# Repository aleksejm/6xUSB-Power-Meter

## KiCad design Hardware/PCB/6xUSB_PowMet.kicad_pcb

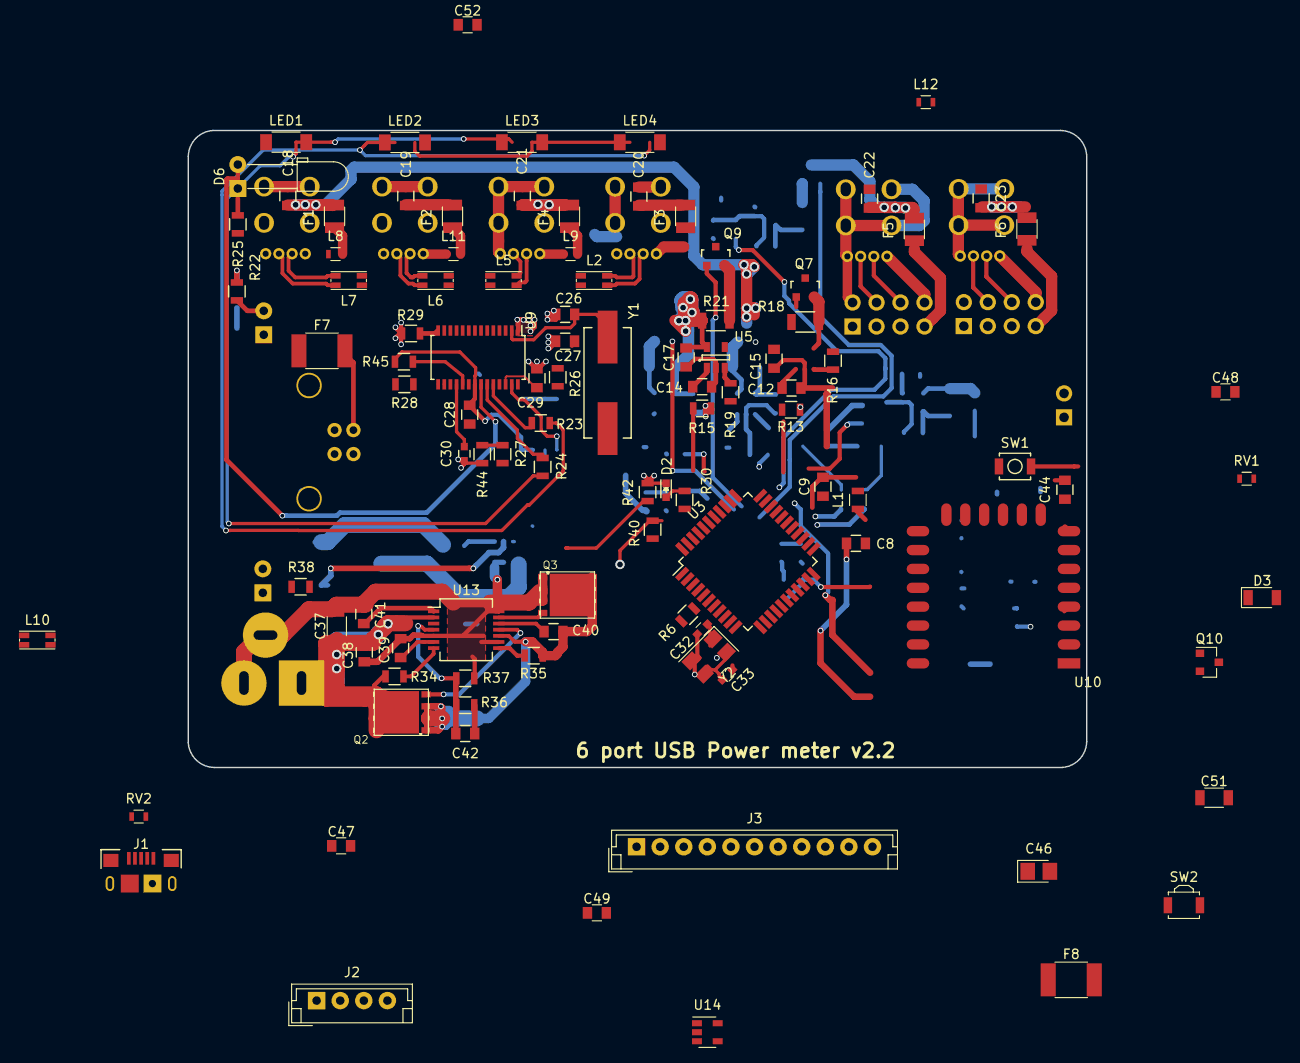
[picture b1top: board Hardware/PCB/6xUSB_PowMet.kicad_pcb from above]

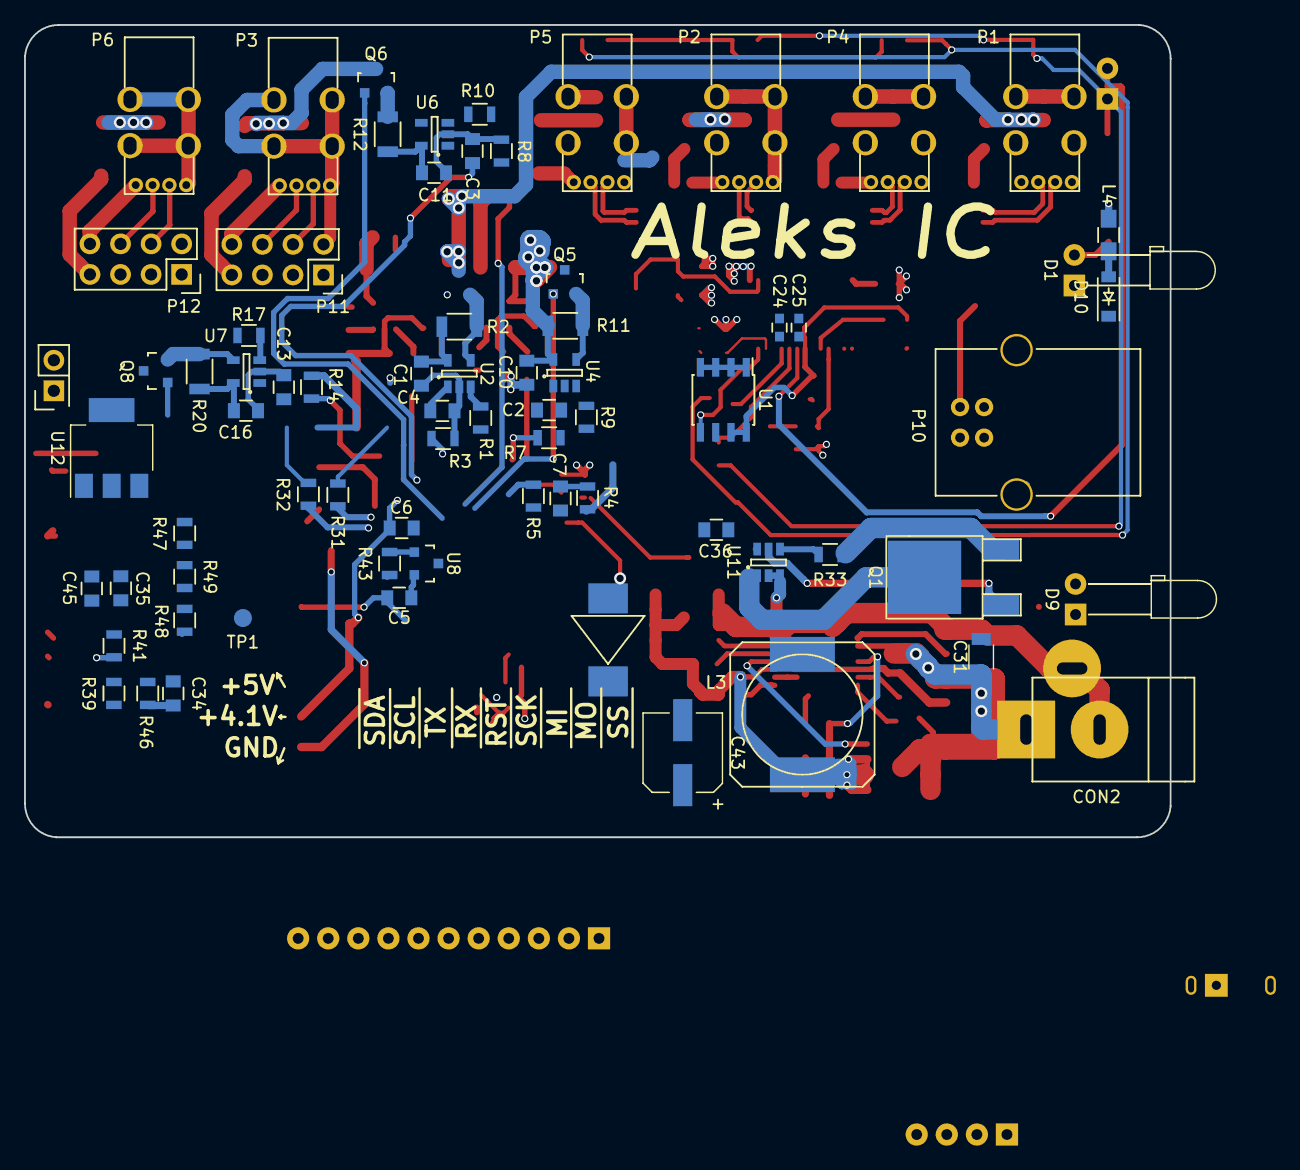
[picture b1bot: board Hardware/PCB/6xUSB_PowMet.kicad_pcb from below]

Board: 4 copper layers, 95.2 x 67.5 mm, 175 parts (73 on the bottom side), 137 nets.

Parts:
C1, C3, C4, C5, C6, C7, C8, C9, C10, C15, C16, C17, C27, C34, C35, C38, C48: 100n; C_0805
C2: 0.33uF; C_0805
C11, C12, C13, C14, C21, C22, C23, C42: 1nF; C_0805
C18, C19, C20, C28, C36, C44, C45: 10uF; C_0805
C24, C30, C33: 0.1uF; C_0603
C25, C32: 22pF; C_0603
C26, C52: 18pF; C_0805
C29: 10nF; C_0805
C31, C37, C51: 47uF; C_1206
C39: 15nF; C_0805
C40: 470nF; C_0805
C41, C47, C49: 1uF; C_0805
C43: 330uF; CP_Elec_6.3x5.8
C46: 22uF; CP_Tantalum_Case-R_EIA-2012-12_Reflow
CON2: BARREL_JACK; JACK_ALIM
D1: USB Power; LED_D3.0mm_Horizontal_O6.35mm_Z6.0mm
D2: MC Status; LED_0603
D3: CD1206-S01575; D_1206
D6: Led_Small_3mm; LED_D3.0mm_Horizontal_O6.35mm_Z6.0mm
D9: Power DC; LED_D3.0mm_Horizontal_O6.35mm_Z6.0mm
D10: SKL14; SOD-123
D11: SK152-TP; DO-214AB-SMC
F1, F2, F3, F4, F5, F6: F_Small; Fuse_SMD1206_Reflow
F7, F8: MSMF050-2; R_1812
J1: MICROUSB; USB-MICRO-B-FCI-10118193
J2: CONN_01X04; JST_EH_B04B-EH-A_04x2.50mm_Straight
J3: CONN_01X11; JST_EH_B11B-EH-A_11x2.50mm_Straight
L1: MH2029-300Y; L_0805
L2, L5, L6, L7, L10: WE-CNSW; L_CommonMode_Wuerth_WE-CNSW
L3: 4.7uH 5.2mOhm; SELF-WE-PD-XXL
L4: Bead/100MHZ/470ohm/2A; R_0805_HandSoldering
L8, L9, L11, L12: WE-CBF; L_0603
LED1, LED2, LED3, LED4: Led_Small; L_1806
P1, P2, P3, P4, P5, P6: USB_A; USB_A_Vertical
P10: USB_B
P11, P12: CONN_02X04; Socket_Strip_Straight_2x04
P13: Burn; Pin_Header_Straight_2x01
Q1: IRFR5305PBF; TO-252-2Lead
Q2: CSD16321Q5; AB2_SON5x6_FET
Q3: CSD18509Q5B; AB2_SON5x6_FET
Q5, Q6, Q7, Q8, Q9, Q10: IRLML6401; SOT-23
R1, R46: 470R; R_0805
R2, R11, R12, R18, R20, R21: 0.02R; R_1206
R3, R4, R6, R8, R9, R10, R13, R15, R16, R17, R19, R26, R27, R30, R37, R39, R40, R42: 10K; R_0805
R5: 15K; R_0805
R7, R32: 22R; R_0805
R14, R22, R23, R24, R25, R41, R43, R44, R47: 100R; R_0805
R28, R38, R45: 100K; R_0805
R29: 2.7K; R_0805
R31: 330; R_0805
R33: 470K; R_0805
R34: 237K; R_0805
R35: 1K07; R_0805
R36: 73K2; R_0805
R48, R49: 150R; R_0805
RV1, RV2: CG0603MLC-05E; L_0603
SW1: Reset; SW_SPST_B3U-1000P
SW2: Reset; SW_SPST_B3U-3000P
TP1: TEST; Measurement_Point_Round-SMD-Pad_Small
U1: 24LC02; SOIC-8_3.9x4.9mm_Pitch1.27mm
U2, U4, U5, U6, U7, U14: LT6106; SOT-23-5
U3: ATMEGA32U4-AU; LQFP-44_10x10mm_Pitch0.8mm
U8: LM4040N-4.1; SOT-23
U9: FE1.1s; TSSOP-28_4.4x9.7mm_Pitch0.65mm
U10: ESP-07v2; ESP-12E
U11: LTC4412; SOT-23-6
U12: 5v to 3.3v LDO; SOT-223-3Lead_TabPin2
U13: LM3150; SSOP-14_5.3x6.2mm_Pitch0.65mm
Y1: 12Mhz; Crystal_HC49-SD_SMD
Y2: 16.000 Mhz; Crystal_SMD_5032-4pin_5.0x3.2mm

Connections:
+3v3: C5.1, C6.1, J2.4, R3.2, R6.2, R10.2, R13.2, TP1.1, U10.8, U12.3
+4.096V: C9.1, C10.1, J2.2, R14.2, U3.42, U8.1
+5V: C2.1, C3.2, C4.2, C8.1, C15.2, C16.2, C17.2, C24.2, C27.2, C33.2, C34.2, C35.2, C48.1, D3.1, D11.2, J2.3, L1.1, Q1.3, R2.1, R4.1, R5.1, R11.1, R12.1, R14.1, R18.1, R20.1, R21.1, R22.1, R24.1, R25.1, R33.1, R41.1, R42.1, R43.1, R44.1, U2.5, U3.2, U3.14, U3.24, U3.34, U4.5, U5.5, U6.5, U7.5, U9.20, U11.6, U12.1, U14.5
/USB hub/3V3: C28.2, R38.1, R45.1, U1.7, U1.8, U9.21
/USB hub/LED1: R47.2, U1.6, U9.23
/USB hub/TESTJ: U1.5, U9.27
ADC9: J3.10, U3.26
ADC10: J3.11, U3.27
D1+: L7.2, P1.3
D1-: L7.3, P1.2
D2+: L6.2, P4.3
D2-: L6.3, P4.2
D3+: L5.2, P2.3
D3-: L5.3, P2.2
D4+: L2.2, P5.3
D4-: L2.3, P5.2
D5+: L10.1, P10.3
D5-: L10.4, P10.2
D+: R7.1, U3.4
D-: R32.1, U3.3
GND: C1.1, C2.2, C3.1, C4.1, C5.2, C6.2, C7.2, C8.2, C9.2, C10.2, C11.1, C12.1, C13.1, C14.1, C15.1, C16.1, C17.1, C18.1, C19.1, C20.1, C21.1, C22.1, C23.1, C24.1, C25.2, C26.1, C27.1, C28.1, C29.2, C31.2, C32.2, C33.1, C34.1, C35.1, C36.1, C37.2, C38.2, C39.2, C41.1, C43.2, C44.1, C45.1, C46.2, C47.1, C48.2, C49.1, C51.2, C52.1, CON2.2, CON2.3, D1.1, D2.1, D9.1, J1.5, J2.1, P1.4, P1.5, P2.4, P2.5, P4.4, P4.5, P5.4, P5.5, P10.4, P10.5, P11.1, P12.1, P13.2, Q3.1, Q3.2, Q3.3, R8.1, R9.1, R15.2, R16.2, R17.2, R19.2, R26.2, R29.2, R30.2, R37.1, R39.2, R40.2, R48.2, RV1.2, RV2.2, SW1.1, SW2.2, U1.1, U1.2, U1.3, U1.4, U2.2, U3.5, U3.15, U3.23, U3.35, U3.43, U4.2, U5.2, U6.2, U7.2, U8.2, U9.1, U10.15, U11.2, U11.3, U12.2, U13.5, U13.9, U13.14, U14.2, Y2.2, Y2.4
MC_ST: R46.1, U3.29
MISO: J3.3, U3.11
MOSI: J3.2, U3.10
unnamed: C1.2, R1.1, R6.1, SW1.2, U10.1
unnamed: C11.2, R5.2, R15.1, U3.30
unnamed: C12.2, R16.1, U2.1, U3.41
unnamed: C13.2, R17.1, U3.39, U4.1
unnamed: C14.2, R19.1, U3.37, U5.1
unnamed: C18.2, F1.2, Q10.3
unnamed: C19.2, F4.2, Q5.3
unnamed: C20.2, F3.2, Q6.3
unnamed: C21.2, R30.1, U3.40, U6.1
unnamed: C22.2, R39.1, U3.36, U7.1
unnamed: C23.2, R40.1, U3.38, U14.1
unnamed: C25.1, U3.16, Y2.3
unnamed: C26.2, U9.2, Y1.1
unnamed: C29.1, R42.2, U9.26
unnamed: C30.1, R28.1
unnamed: C30.2, R27.2, R28.2, U9.18
unnamed: C31.1, C37.1, C38.1, C51.1, CON2.1, Q2.5, Q2.6, Q2.7, Q2.8, R34.2, U13.2
unnamed: C32.1, U3.17, Y2.1
unnamed: C36.2, F2.2, Q7.3
unnamed: C39.1, U13.6
unnamed: C40.1, L3.1, Q2.1, Q2.2, Q2.3, Q3.5, Q3.6, Q3.7, Q3.8, R35.1, U13.10
unnamed: C40.2, U13.12
unnamed: C41.2, U13.1
unnamed: C42.1, C43.1, D11.1, L3.2, R31.1, R36.2
unnamed: C42.2, R36.1, R37.2, U13.4
unnamed: C44.2, F5.2, Q9.3
unnamed: C45.2, F6.2, Q8.3
unnamed: C46.1, F8.1, J1.1
unnamed: C47.2, L1.2, U3.44
unnamed: C49.2, U3.6
unnamed: C52.2, U9.3, Y1.2
unnamed: D1.2, R49.2
unnamed: D2.2, R46.2
unnamed: D6.1, R48.1
unnamed: D6.2, LED1.2, LED2.1, LED3.2, LED4.1, U9.22
unnamed: D9.2, R31.2
unnamed: D10.2, L4.1
unnamed: F1.1, L8.2
unnamed: F2.1, L11.2
unnamed: F3.1, P11.7
unnamed: F4.1, L9.2
unnamed: F5.1, L12.2
unnamed: F6.1, P12.7
unnamed: F7.2, P10.1
unnamed: J1.2, R32.2, RV2.1
unnamed: J1.3, R7.2, RV1.1
unnamed: L2.1, U9.5
unnamed: L2.4, U9.4
unnamed: L5.1, U9.7
unnamed: L5.4, U9.6
unnamed: L6.1, U9.9
unnamed: L6.4, U9.8
unnamed: L7.1, U9.11
unnamed: L7.4, U9.10
unnamed: L8.1, P1.1
unnamed: L9.1, P2.1
unnamed: L10.2, U9.16
unnamed: L10.3, U9.15
unnamed: L11.1, P4.1
unnamed: L12.1, P5.1
unnamed: LED1.1, LED4.2, R23.1
unnamed: LED2.2, LED3.1, R47.1
unnamed: P3.4, P3.5, P11.2
unnamed: P3.3, P11.4
unnamed: P3.2, P11.6
unnamed: P3.1, P11.8
unnamed: P6.4, P6.5, P12.2
unnamed: P6.3, P12.4
unnamed: P6.2, P12.6
unnamed: P6.1, P12.8
unnamed: P13.1, R10.1, U10.18
unnamed: Q1.1, U11.5
unnamed: Q2.4, U13.11
unnamed: Q3.4, U13.13
unnamed: Q5.2, R11.2, U4.4
unnamed: Q6.2, R12.2, U5.4
unnamed: Q7.2, R18.2, U6.4
unnamed: Q8.2, R20.2, U7.4
unnamed: Q9.2, R21.2, U14.4
unnamed: Q10.2, R2.2, U2.4
unnamed: R1.2, U10.4
unnamed: R3.1, U10.3
unnamed: R9.2, U10.16
unnamed: R13.1, U10.17
unnamed: R22.2, U2.3
unnamed: R23.2, U9.24
unnamed: R24.2, U4.3
unnamed: R25.2, U5.3
unnamed: R29.1, U9.14
unnamed: R34.1, U13.7
unnamed: R35.2, U13.8
unnamed: R38.2, U9.17
unnamed: R41.2, U6.3
unnamed: R43.2, U7.3
unnamed: R44.2, U14.3
unnamed: R45.2, U9.19
PB0_40: R26.1, R33.2, U3.28, U11.4
RST: D3.2, J3.5, R4.2, SW2.1, U3.13
RXD: J3.6, U3.20, U10.22
SCK: J3.4, U3.9
SCL: J3.8, U3.18
SDA: J3.9, U3.19
SS: J3.1, U3.8
TXD: J3.7, U3.21, U10.21
USB_1: Q10.1, U3.1
USB_2: Q7.1, U3.12
USB_3: Q5.1, U3.32
USB_4: Q9.1, U3.33
USB_5: Q6.1, U3.31
USB_6: Q8.1, U3.22
USB_P: F7.1, L4.2, R49.1, U3.25
VBUS: C7.1, F8.2, R8.2, U3.7
VREG: D10.1, Q1.2, R27.1, U11.1

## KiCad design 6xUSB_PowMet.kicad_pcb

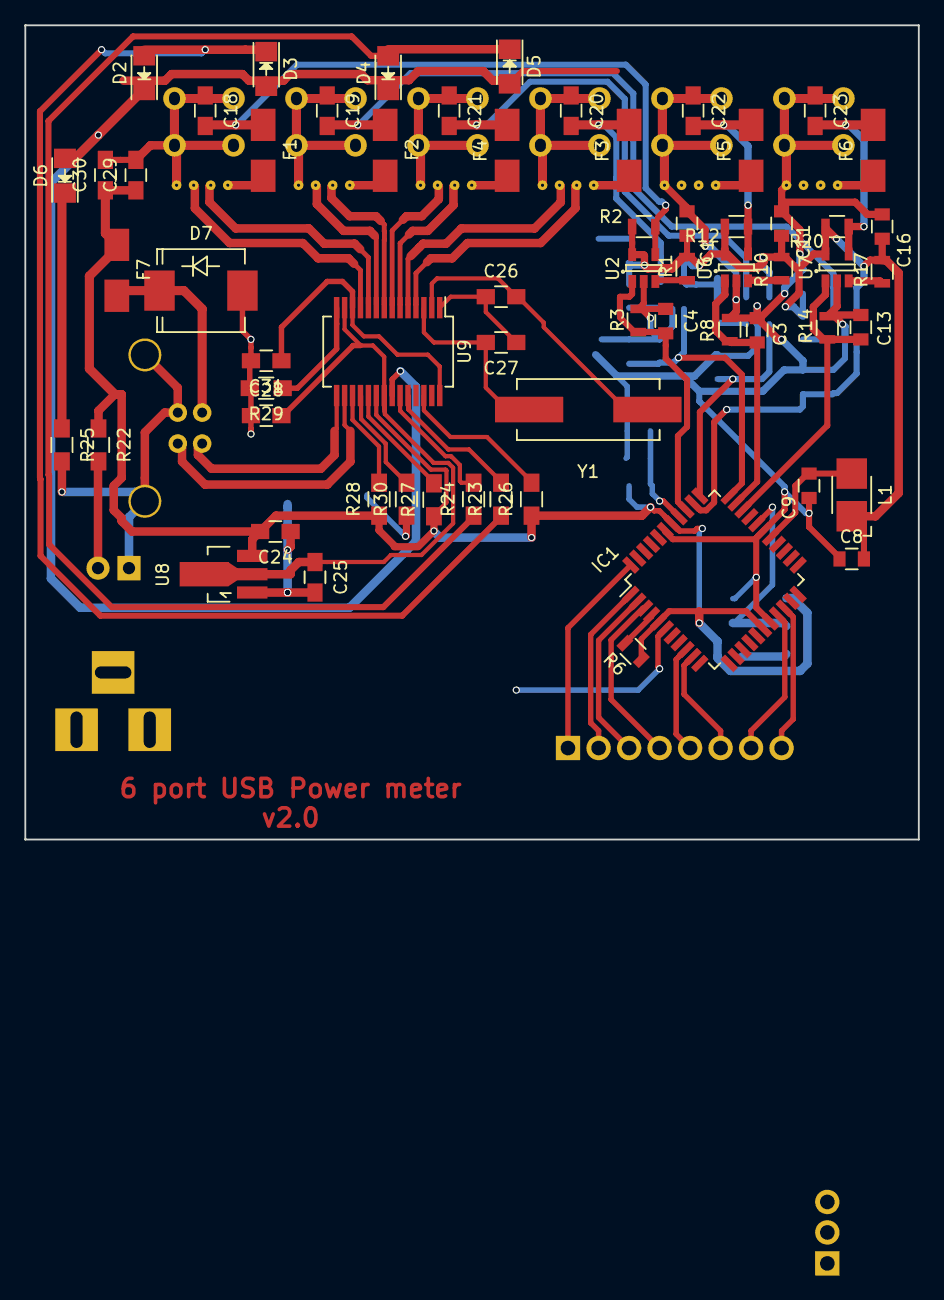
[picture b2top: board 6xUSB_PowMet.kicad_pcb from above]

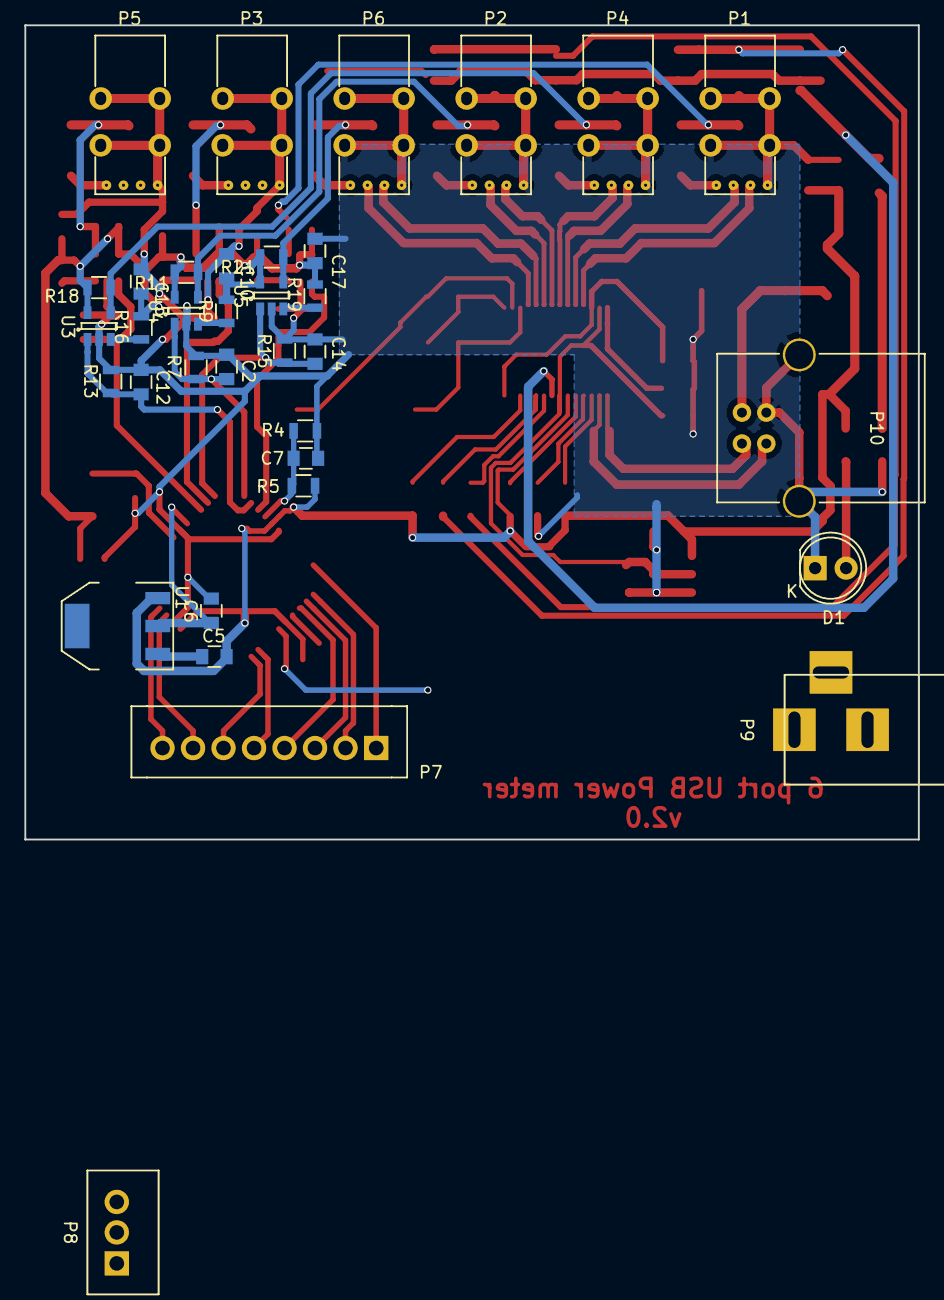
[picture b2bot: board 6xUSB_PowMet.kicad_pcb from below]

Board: 2 copper layers, 73.2 x 66.8 mm, 97 parts (35 on the bottom side), 65 nets.

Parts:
C1, C5, C8, C9, C10, C11, C15, C16, C17: 100n; C_0805
C2, C3, C4, C7, C12, C13, C14: 1n; C_0805
C6: 10uF; C_0805
C18, C19, C20, C21, C22, C23, C28, C30, C31: 10uF; C_0805_HandSoldering
C24, C25: 4.7uF; C_0805_HandSoldering
C26, C27: 10pF; C_0805_HandSoldering
C29: 10nF; C_0805_HandSoldering
D1: Power; LED-5MM
D2, D3, D4, D5, D6: Led_Small; LED_1206
D7: 5.1V; SMC_Standard
F1, F2, F3, F4, F5, F6, F7: F_Small; Fuse_SMD1206_HandSoldering
IC1: ATMEGA32-M; TQFP-44_10x10mm_Pitch0.8mm
L1: 10uH; Inductor_1212
P1, P2, P3, P4, P5, P6: USB_A; USB_A_Vertical
P7: CONN_01X08; Wafer_Vertical22.5x5.8x7RM2.5-8
P8: CONN_01X03; Wafer_Vertical10x5.8x7RM2.5-3
P9: CONN_01X02; BARREL_JACK
P10: USB_B
R1, R9, R10, R16, R17, R19: 100R; R_0805
R2, R11, R12, R18, R20, R21: 0.01R; R_0805
R3, R4, R7, R8, R13, R14, R15: 10K; R_0805
R5: 14K; R_0805
R6: 10k; R_0805
R22, R23, R24, R25: 330; R_0805_HandSoldering
R26, R27, R28, R30: 10K; R_0805_HandSoldering
R29: 2.7K; R_0805_HandSoldering
U1: LM1117MP-2.5; SOT-223
U2, U3, U4, U5, U6, U7: LT6106; SOT-23-5
U8: AP1117E33; SOT89-3_Housing_Handsoldering
U9: FE1.1s; SSOP-28_5.3x10.2mm_Pitch0.65mm
Y1: 12Mhz; Crystal_HC49-SD_SMD

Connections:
+2.5V: C6.1, IC1.29, P8.2, U1.2
+5V: C1.2, C5.1, C8.2, C10.2, C11.2, C15.2, C16.2, C17.2, C24.2, C29.1, C30.1, D7.1, F7.1, F7.2, IC1.5, IC1.17, IC1.38, L1.1, P8.3, P9.1, P10.1, R1.1, R2.1, R5.1, R6.1, R9.1, R10.1, R11.1, R12.1, R16.1, R17.1, R18.1, R19.1, R20.1, R21.1, R22.1, R26.1, R27.1, R28.1, U1.3, U2.5, U3.5, U4.5, U5.5, U6.5, U7.5, U8.3, U9.20
/USB hub/1V8: C31.1, U9.12, U9.28
/USB hub/3V3: C25.1, C28.2, U8.2, U9.13, U9.21
D1+: P1.3, U9.11
D1-: P1.2, U9.10
D2+: P4.3, U9.9
D2-: P4.2, U9.8
D3+: P2.3, U9.7
D3-: P2.2, U9.6
D4+: P6.3, U9.5
D4-: P6.2, U9.4
D5+: P10.3, U9.16
D5-: P10.2, U9.15
GND: C1.1, C2.1, C3.1, C4.1, C5.2, C6.2, C7.1, C8.1, C9.1, C10.1, C11.1, C12.1, C13.1, C14.1, C15.1, C16.1, C17.1, C18.1, C19.1, C20.1, C21.1, C22.1, C23.1, C24.1, C25.2, C28.1, C29.2, C30.2, C31.2, D1.1, D7.2, IC1.6, IC1.18, IC1.28, IC1.39, P1.4, P1.5, P2.4, P2.5, P3.4, P3.5, P4.4, P4.5, P5.4, P5.5, P6.4, P6.5, P8.1, P9.2, P10.4, P10.5, R3.1, R4.1, R7.1, R8.1, R13.1, R14.1, R15.1, R25.2, R29.2, R30.1, U1.1, U2.2, U3.2, U4.2, U5.2, U6.2, U7.2, U8.1
MISO: IC1.2, P7.3
MOSI: IC1.1, P7.2
unnamed: C2.2, IC1.34, R7.2, U4.1
unnamed: C3.2, IC1.32, R8.2, U6.1
unnamed: C4.2, IC1.36, R3.2, U2.1
unnamed: C7.2, IC1.37, R4.2, R5.2
unnamed: C9.2, IC1.27, L1.2
unnamed: C12.2, IC1.35, R13.2, U3.1
unnamed: C13.2, IC1.31, R14.2, U7.1
unnamed: C14.2, IC1.33, R15.2, U5.1
unnamed: C18.2, F1.1, R2.2, U2.4
unnamed: C19.2, F2.1, R18.2, U3.4
unnamed: C20.2, F3.2, R21.2, U5.4
unnamed: C21.2, F4.2, R11.2, U4.4
unnamed: C22.2, F5.2, R12.2, U6.4
unnamed: C23.2, F6.2, R20.2, U7.4
unnamed: C26.1, C27.1, U9.1
unnamed: C26.2, U9.2, Y1.1
unnamed: C27.2, U9.3, Y1.2
unnamed: D1.2, R22.2
unnamed: D2.1, D3.2, D4.1, D5.2, D6.2, U9.22
unnamed: D2.2, D3.1, R23.1
unnamed: D4.2, D5.1, R24.1
unnamed: D6.1, R25.1
unnamed: F1.2, P1.1
unnamed: F2.2, P4.1
unnamed: F3.1, P6.1
unnamed: F4.1, P2.1
unnamed: F5.1, P3.1
unnamed: F6.1, P5.1
unnamed: IC1.4, R6.2
unnamed: R1.2, U2.3
unnamed: R9.2, U4.3
unnamed: R10.2, U6.3
unnamed: R16.2, U3.3
unnamed: R17.2, U7.3
unnamed: R19.2, U5.3
unnamed: R23.2, U9.24
unnamed: R24.2, U9.23
unnamed: R26.2, U9.26
unnamed: R27.2, U9.19
unnamed: R28.2, U9.17
unnamed: R29.1, U9.14
unnamed: R30.2, U9.18
RXD: IC1.9, P7.5
SCK: IC1.3, P7.4
SCL: IC1.19, P7.7
SDA: IC1.20, P7.8
SS: IC1.44, P7.1
TXD: IC1.10, P7.6

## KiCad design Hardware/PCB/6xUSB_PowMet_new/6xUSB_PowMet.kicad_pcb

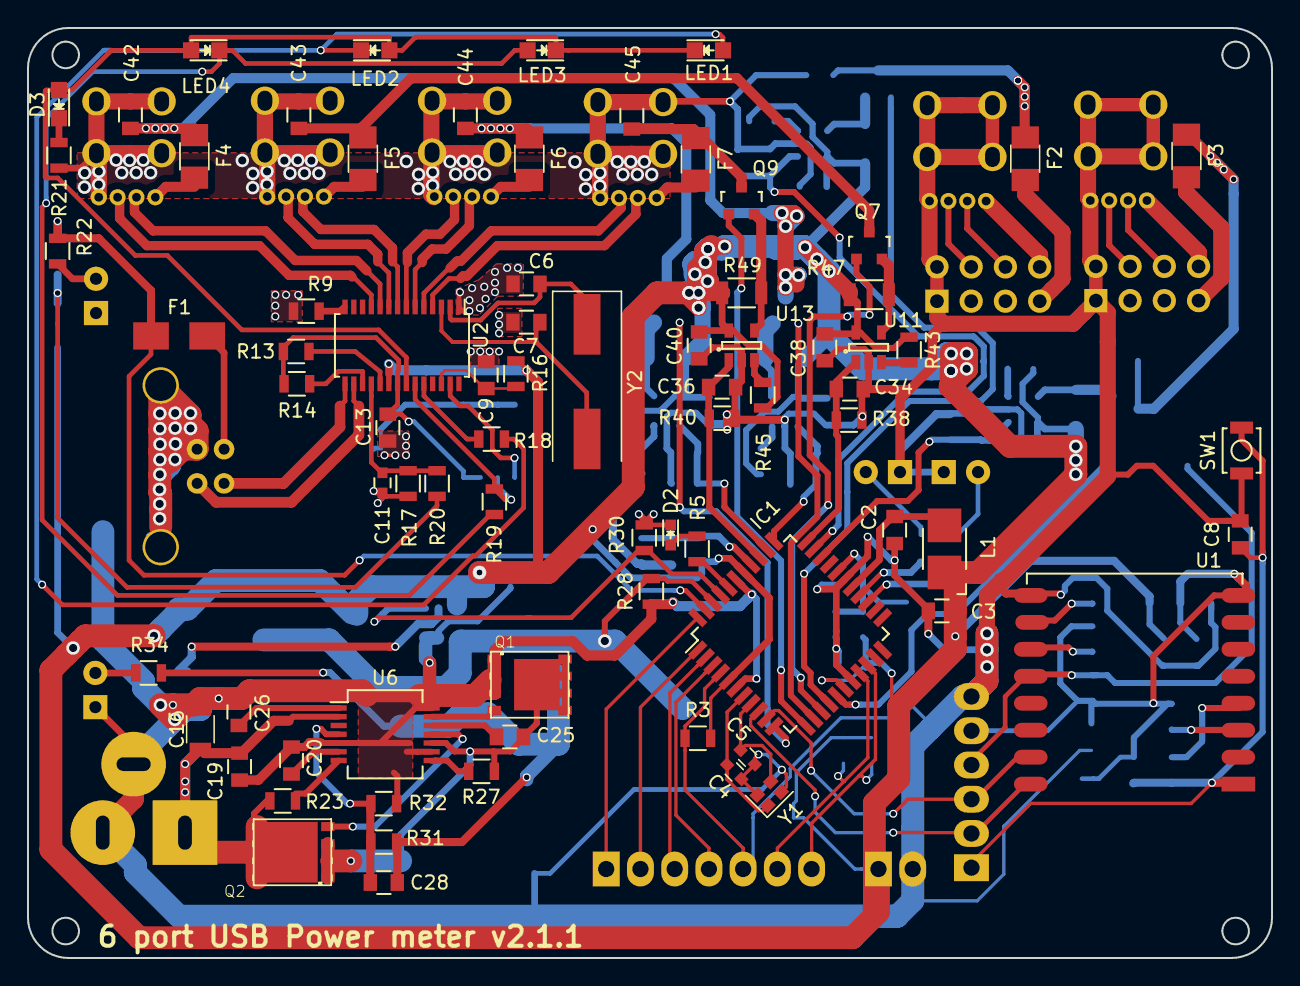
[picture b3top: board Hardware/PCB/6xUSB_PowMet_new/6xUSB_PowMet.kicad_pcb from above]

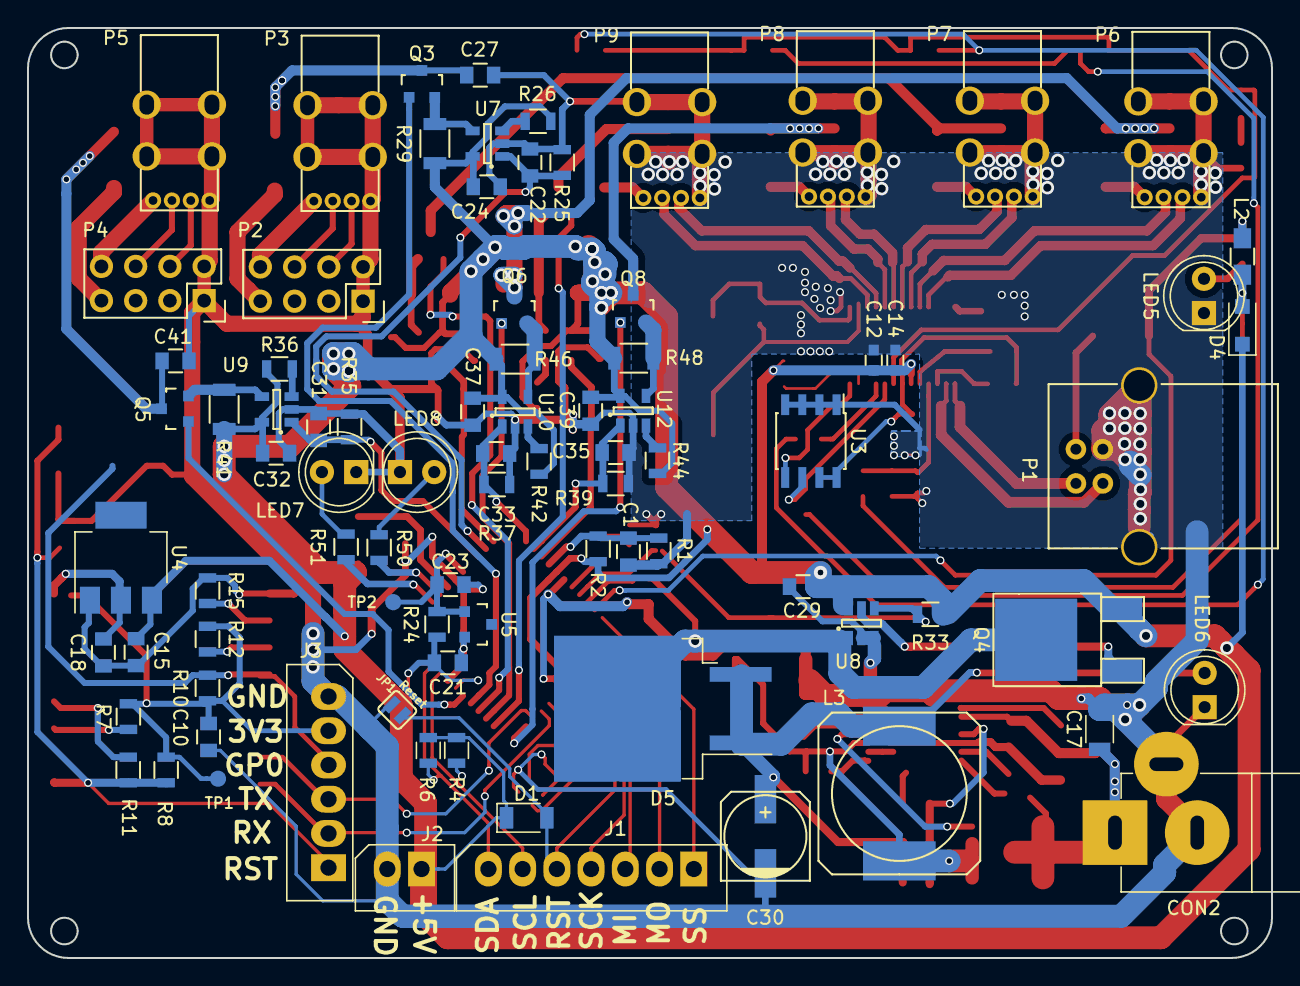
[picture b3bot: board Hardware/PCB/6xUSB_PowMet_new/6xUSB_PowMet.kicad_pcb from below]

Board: 2 copper layers, 92.3 x 69.0 mm, 161 parts (85 on the bottom side), 115 nets.

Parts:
C1: 1n; C_0805
C2, C3, C8, C21, C23: 100n; C_0805
C4, C5: 22pF; C_0603
C6, C7: 18pF; C_0805
C9: 10nF; C_0805
C10: 100uF; C_0805
C11, C12, C14: 0.1uF; C_0603
C13, C15, C27, C41, C42, C43, C44, C45: 10uF; C_0805
C16, C17: 22uF; C_1206
C18, C19, C24, C29, C32, C37, C38, C39, C40: 100nF; C_0805
C20: 15nF; C_0805
C22, C31, C33, C34, C35, C36: 1nF; C_0805
C25: 470nF; C_0805
C26: 1uF; C_0805
C28: 470pF; C_0805
C30: 220uF; c_elec_6.3x7.7
CON2: JACK; JACK_ALIM
D1: CD1206-S01575; D_1206
D2: MC Stat; LED_0603
D3: Act; LED_0805
D4: SKL14; D_SOD-123F
D5: SK2030YD2; TO-263-2
F1: 500mA; Fuse_SMD1206_HandSoldering
F2, F3, F4, F5, F6, F7: F_Small; Fuse_SMD1206_Wave
IC1: ATMEGA32-M; TQFP-44_10x10mm_Pitch0.8mm
J1: Conn_01x07; Molex_SPOX-5267_22-03-5075_07x2.54mm_Straight
J2: Conn_01x02; Molex_SPOX-5267_22-03-5025_02x2.54mm_Straight
J3: Conn_01x06; Molex_SPOX-5267_22-03-5065_06x2.54mm_Straight
JP1: Reset; SMT-JUMPER_2_NO_SILK
L1: 10uH; Inductor_1212
L2: 100Mhz 470ohm; R_0805_HandSoldering
L3: 2.2uH; SELF-WE-PD-XXL
LED1: P4; LED_0805
LED2: P2; LED_0805
LED3: P3; LED_0805
LED4: P1; LED_0805
LED5: U_PW; LED_D5.0mm
LED6: DC_PW; LED_D5.0mm
LED7: ST_USB; LED_D5.0mm
LED8: ST_DC; LED_D5.0mm
P1: USB_B
P2, P4: CONN_02X04; Socket_Strip_Straight_2x04
P3, P5, P6, P7, P8, P9: USB_A; USB_A_Vertical
Q1: CSD17577Q5A; AB2_SON5x6_FET
Q2: CSD16342Q5A; AB2_SON5x6_FET
Q3, Q5, Q6, Q7, Q8, Q9: IRLML6401; SOT-23
Q4: IRFR5305PBF; TO-252-2Lead
R1, R3, R4, R6, R7, R8, R10, R12, R15, R16, R20, R28, R30, R32: 10K; R_0805
R2: 15K; R_0805
R5, R11, R18, R19, R21, R22, R34, R50, R51: 470; R_0805
R9: 2.7K; R_0805
R13, R14, R17, R23: 100K; R_0805
R24: 100; R_0805
R25, R35, R37, R38, R39, R40: 1K; R_0805
R26, R36, R42, R43, R44, R45: 100R; R_0805
R27: 1K07; R_0805
R29, R41, R46, R47, R48, R49: 0.02R; R_1206
R31: 73K2; R_0805
R33: 470K; R_0805
SW1: Reset; SW_SPST_B3U-1000P
TP1: 3.3V; TEST-SMD-SMALL
TP2: 4.096V; TEST-SMD-SMALL
U1: ESP-12; ESP-12_mod
U2: FE1.1s; TSSOP-28_4.4x9.7mm_Pitch0.65mm
U3: 24LC02; SOIC-8_3.9x4.9mm_Pitch1.27mm
U4: AP1117E33; SOT-223
U5: LM4040; SOT-23
U6: LM3150; SSOP-14_5.3x6.2mm_Pitch0.65mm
U7, U9, U10, U11, U12, U13: LT6106; SOT-23-5
U8: LTC4412; SOT-23-6
Y1: 16MHz; Crystal_SMD_2016-4pin_2.0x1.6mm
Y2: 12Mhz; Crystal_SMD_HC49-SD

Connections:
+3V3: C10.1, C18.1, J3.5, R7.1, R8.1, R10.1, R12.1, TP1.1, U1.8, U4.2
+5V: C3.2, C12.2, C14.2, C15.1, C21.1, C24.2, C29.1, C32.2, C37.2, C38.2, C39.2, C40.2, D1.1, D4.1, IC1.5, IC1.17, IC1.38, J2.1, L1.1, Q4.3, R2.1, R3.2, R4.1, R6.1, R16.2, R24.2, R26.2, R29.1, R33.1, R36.2, R41.1, R42.2, R43.2, R44.2, R45.2, R46.1, R47.1, R48.1, R49.1, U2.20, U4.3, U7.5, U8.6, U9.5, U10.5, U11.5, U12.5, U13.5
/3V3: C13.1, R13.1, R14.1, U2.21, U3.7, U3.8
/+4.096V: C23.1, IC1.29, R24.1, TP2.1, U5.1
/D+1: P6.3, U2.11
/D+2: P7.3, U2.9
/D+3: P8.3, U2.7
/D+4: P9.3, U2.5
/D+5: P1.3, U2.16
/D-1: P6.2, U2.10
/D-2: P7.2, U2.8
/D-3: P8.2, U2.6
/D-4: P9.2, U2.4
/D-5: P1.2, U2.15
/GPIO0: J3.4, R10.2, U1.12
/LED1: R19.2, U2.23, U3.6
/MC_ST: IC1.40, R5.1
/MISO: IC1.2, J1.3
/MOSI: IC1.1, J1.2
/PB0_40: IC1.41, R30.1, R33.2, U8.4
/PB1_41: D5.2, IC1.42, Q4.2, R28.2, U8.1
/RST-ESP: C8.1, J3.1, R8.2, R11.2, SW1.2, U1.1
/RXD: IC1.9, J3.2, U1.16
/Reset: D1.2, IC1.4, J1.5, JP1.1, R3.1
/SCK: IC1.3, J1.4
/SCL: IC1.19, J1.6, R4.2
/SDA: IC1.20, J1.7, R6.2
/SS: IC1.44, J1.1
/ST_DC: IC1.26, R50.1
/ST_USB: IC1.25, R51.1
/TESTJ: U2.27, U3.5
/TXD: IC1.10, J3.3, U1.15
/USB1: IC1.13, Q6.1
/USB2: IC1.14, Q7.1
/USB3: IC1.11, Q8.1
/USB4: IC1.12, Q9.1
/USB5: IC1.16, Q5.1
/USB6: IC1.15, Q3.1
/USB_P: F1.1, IC1.43, L2.1, R22.1
/U_Sens1: C33.1, IC1.34, R37.1, U10.1
/U_Sens2: C34.1, IC1.33, R38.1, U11.1
/U_Sens3: C35.1, IC1.35, R39.1, U12.1
/U_Sens4: C36.1, IC1.36, R40.1, U13.1
/U_Sens5: C31.1, IC1.31, R35.1, U9.1
/U_Sens6: C22.1, IC1.32, R25.1, U7.1
/VBUSM: D4.2, L2.2, R20.1
GND: C1.1, C2.1, C3.1, C4.1, C5.1, C6.2, C7.2, C8.2, C9.1, C10.2, C11.2, C12.1, C13.2, C14.1, C15.2, C16.2, C17.2, C18.2, C19.2, C20.1, C21.2, C22.2, C23.2, C24.1, C26.1, C27.2, C29.2, C30.2, C31.2, C32.1, C33.2, C34.2, C35.2, C36.2, C37.1, C38.1, C39.1, C40.1, C41.2, C42.2, C43.2, C44.2, C45.2, CON2.2, CON2.3, D2.1, IC1.6, IC1.18, IC1.28, IC1.39, J2.2, J3.6, JP1.2, LED5.1, LED6.1, LED7.1, LED8.1, P1.4, P1.5, P2.1, P2.2, P3.4, P3.5, P4.1, P4.2, P5.4, P5.5, P6.4, P6.5, P7.4, P7.5, P8.4, P8.5, P9.4, P9.5, Q1.1, Q1.2, Q1.3, R1.1, R9.1, R15.1, R17.1, R21.2, R25.2, R28.1, R30.2, R32.1, R35.2, R37.2, R38.2, R39.2, R40.2, SW1.1, U1.9, U2.1, U3.1, U3.2, U3.3, U3.4, U4.1, U5.2, U6.5, U6.9, U6.14, U7.2, U8.2, U8.3, U9.2, U10.2, U11.2, U12.2, U13.2, Y1.2, Y1.4
unnamed: C1.2, IC1.37, R1.2, R2.2
unnamed: C2.2, IC1.27, L1.2
unnamed: C4.2, IC1.7, Y1.1
unnamed: C5.2, IC1.8, Y1.3
unnamed: C6.1, U2.2, Y2.1
unnamed: C7.1, U2.3, Y2.2
unnamed: C9.2, R16.1, U2.26
unnamed: C11.1, R17.2, R20.2, U2.18
unnamed: C16.1, C17.1, C19.1, CON2.1, Q2.5, Q2.6, Q2.7, Q2.8, R23.2, U6.2
unnamed: C20.2, U6.6
unnamed: C25.1, L3.1, Q1.5, Q1.6, Q1.7, Q1.8, Q2.1, Q2.2, Q2.3, R27.1, U6.10
unnamed: C25.2, U6.12
unnamed: C26.2, U6.1
unnamed: C27.1, F2.1, Q3.3
unnamed: C28.1, C30.1, D5.1, D5.3, L3.2, R31.2, R34.1
unnamed: C28.2, R31.1, R32.2, U6.4
unnamed: C41.1, F3.1, Q5.3
unnamed: C42.1, F4.1, Q6.3
unnamed: C43.1, F5.1, Q7.3
unnamed: C44.1, F6.1, Q8.3
unnamed: C45.1, F7.1, Q9.3
unnamed: D2.2, R5.2
unnamed: D3.1, R21.1
unnamed: D3.2, LED1.1, LED2.2, LED3.1, LED4.2, U2.22
unnamed: F1.2, P1.1
unnamed: F2.2, P2.7
unnamed: F3.2, P4.7
unnamed: F4.2, P6.1
unnamed: F5.2, P7.1
unnamed: F6.2, P8.1
unnamed: F7.2, P9.1
unnamed: LED1.2, LED2.1, R18.1
unnamed: LED3.2, LED4.1, R19.1
unnamed: LED5.2, R22.2
unnamed: LED6.2, R34.2
unnamed: LED7.2, R51.2
unnamed: LED8.2, R50.2
unnamed: P2.4, P3.3
unnamed: P2.6, P3.2
unnamed: P2.8, P3.1
unnamed: P4.4, P5.3
unnamed: P4.6, P5.2
unnamed: P4.8, P5.1
unnamed: Q1.4, U6.13
unnamed: Q2.4, U6.11
unnamed: Q3.2, R29.2, U7.4
unnamed: Q4.1, U8.5
unnamed: Q5.2, R41.2, U9.4
unnamed: Q6.2, R46.2, U10.4
unnamed: Q7.2, R47.2, U11.4
unnamed: Q8.2, R48.2, U12.4
unnamed: Q9.2, R49.2, U13.4
unnamed: R7.2, U1.3
unnamed: R9.2, U2.14
unnamed: R11.1, U1.4
unnamed: R12.2, U1.11
unnamed: R13.2, U2.19
unnamed: R14.2, U2.17
unnamed: R15.2, U1.10
unnamed: R18.2, U2.24
unnamed: R23.1, U6.7
unnamed: R26.1, U7.3
unnamed: R27.2, U6.8
unnamed: R36.1, U9.3
unnamed: R42.1, U10.3
unnamed: R43.1, U11.3
unnamed: R44.1, U12.3
unnamed: R45.1, U13.3

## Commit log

2016-04-18 :boom::camel: Added .gitattributes & .gitignore files
2016-04-18 Revert ":boom::camel: Added .gitattributes & .gitignore files"
    This reverts commit ec87cd9a793b3f8b229a42348b66e58fb7790340.
2016-04-20 6 port USB power meter with OLED display
    6 port USB power meter/PSU with OLED display
2016-05-06 Schematic updates
2016-05-16 Removed some files
2016-05-26 Updated pcb
    Updated schematic and solved some pcb mistakes
2016-05-31 Upd_sch
    Updated schematic and PCB
2016-06-01 Updates schematic
    Updated schematic and added datasheets
2016-06-07 Upd
    Schematic updates and PCB
